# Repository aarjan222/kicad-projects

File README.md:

# kicad-projects
Please read text file of each sub files if seen, like driLL_siZE.txt file.

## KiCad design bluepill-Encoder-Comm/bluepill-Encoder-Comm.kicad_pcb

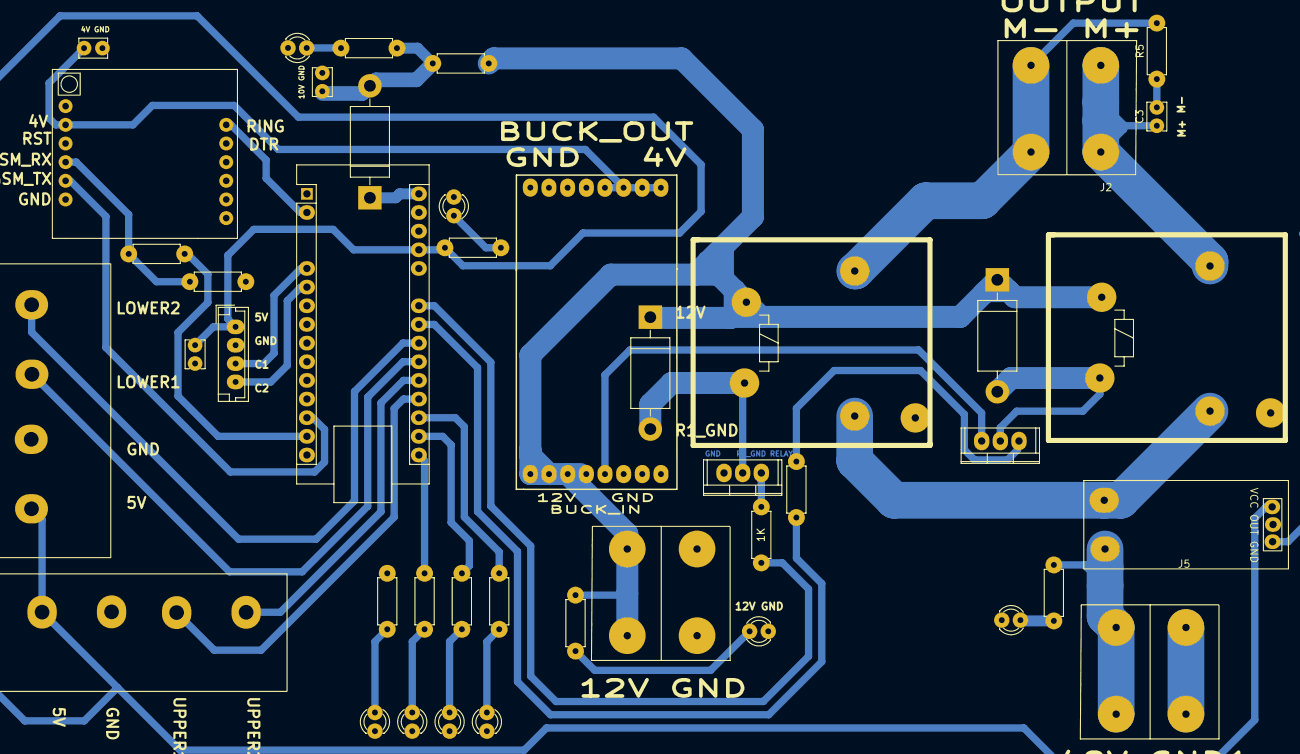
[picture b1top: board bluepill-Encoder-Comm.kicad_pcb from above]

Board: 2 copper layers, 43 parts (0 on the bottom side), 39 nets.

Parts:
1K: R; Resistor_small
A2: Arduino_Nano_v2.x; Arduino_Nano
C3, C4, C5, C6: C_Small; Capacitor_Disc_Small
D1, D2, D3: D_Small; Diode_Medium
D4, D5, D6, D7, D8, D9, D10, D11: LED; LED_D3.0mm
J2, J7, J11: Conn_01x02_Pin; Solar_Connector
J3, J4: Conn_01x04_Pin; Barrier_Terminal_Block
J5: Conn_02x03_Odd_Even; current sensor
J8: Conn_01x04; jst_4
Q1, Q2: TIP122; Voltage_Regulators
R1: 5; Resistor_small
R2, R3: 1K; Resistor_small
R4: 2K; Resistor_small
R5, R9, R10, R11, R12, R13: R_Small; Resistor_small
R6, R7, R8: 220; Resistor_small
Rly1, Rly2: 6V_Relay; Relay_HLS_MEDIUM
U1: SIM800L-CORE
U3: Buck; Buck_Regulator

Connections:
+4V: C5.1, U1.2 (VCC), U3.3 (OUT(+))
+5V: A2.27 (+5V), C6.1, J3.4, J4.4, J5.3, J8.1, R9.1
+10V: C4.1, D2.2 (A), R1.1, R8.1
+12V: D1.1 (K), D3.1 (K), J7.1, R1.2, R7.1, Rly1.2, Rly2.2, U3.1 (IN(+))
+48V: J5.1, J11.1, R6.1
/10V_regulated: A2.30 (VIN), D2.1 (K)
/+48V_I: J5.1, Rly1.1, Rly2.1
/C1: A2.5 (D2), J8.3
/C2: A2.6 (D3), J8.4
/GSM_RX: R2.1, R4.1, U1.4 (RXD)
/GSM_TX: A2.13 (D10), U1.5 (TXD)
/I1: A2.17 (3V3), R10.1
/I2: A2.18 (AREF), R11.1
/I3: A2.16 (D13), R12.1
/LOWER1: A2.21 (A2), J4.2
/LOWER2: A2.22 (A3), J4.1
/M+: C3.1, J2.1
/M-: J2.2, R5.2, Rly2.7
/R1_GND: D1.2 (A), Q1.2 (C), Rly1.6
/R2_GND: D3.2 (A), Q2.2 (C), Rly2.6
/RELAY1: A2.23 (A4), R3.1
/RELAY2: 1K.1, A2.24 (A5)
/RING: A2.2 (D0/RX), U1.12 (RING)
/UPPER1: A2.20 (A1), J3.1
/UPPER2: A2.19 (A0), J3.2
GND: A2.29 (GND), C4.2, C5.2, C6.2, D5.1 (K), D6.1 (K), D7.1 (K), D8.1 (K), D9.1 (K), D10.1 (K), D11.1 (K), J3.3, J4.3, J5.5, J7.2, J8.2, Q1.3 (E), Q2.3 (E), R4.2, U1.6 (GND), U3.2 (IN(-)), U3.4 (OUT(-))
GND1: D4.1 (K), J11.2, Rly1.14, Rly2.14
unnamed: A2.14 (D11), R2.2
unnamed: C3.2, R5.1
unnamed: D4.2 (A), R6.2
unnamed: D5.2 (A), R7.2
unnamed: D6.2 (A), R8.2
unnamed: D7.2 (A), R9.2
unnamed: D8.2 (A), R10.2
unnamed: D9.2 (A), R11.2
unnamed: D10.2 (A), R12.2
unnamed: D11.2 (A), R13.2
unnamed: Q1.1 (B), R3.2
unnamed: 1K.2, Q2.1 (B)

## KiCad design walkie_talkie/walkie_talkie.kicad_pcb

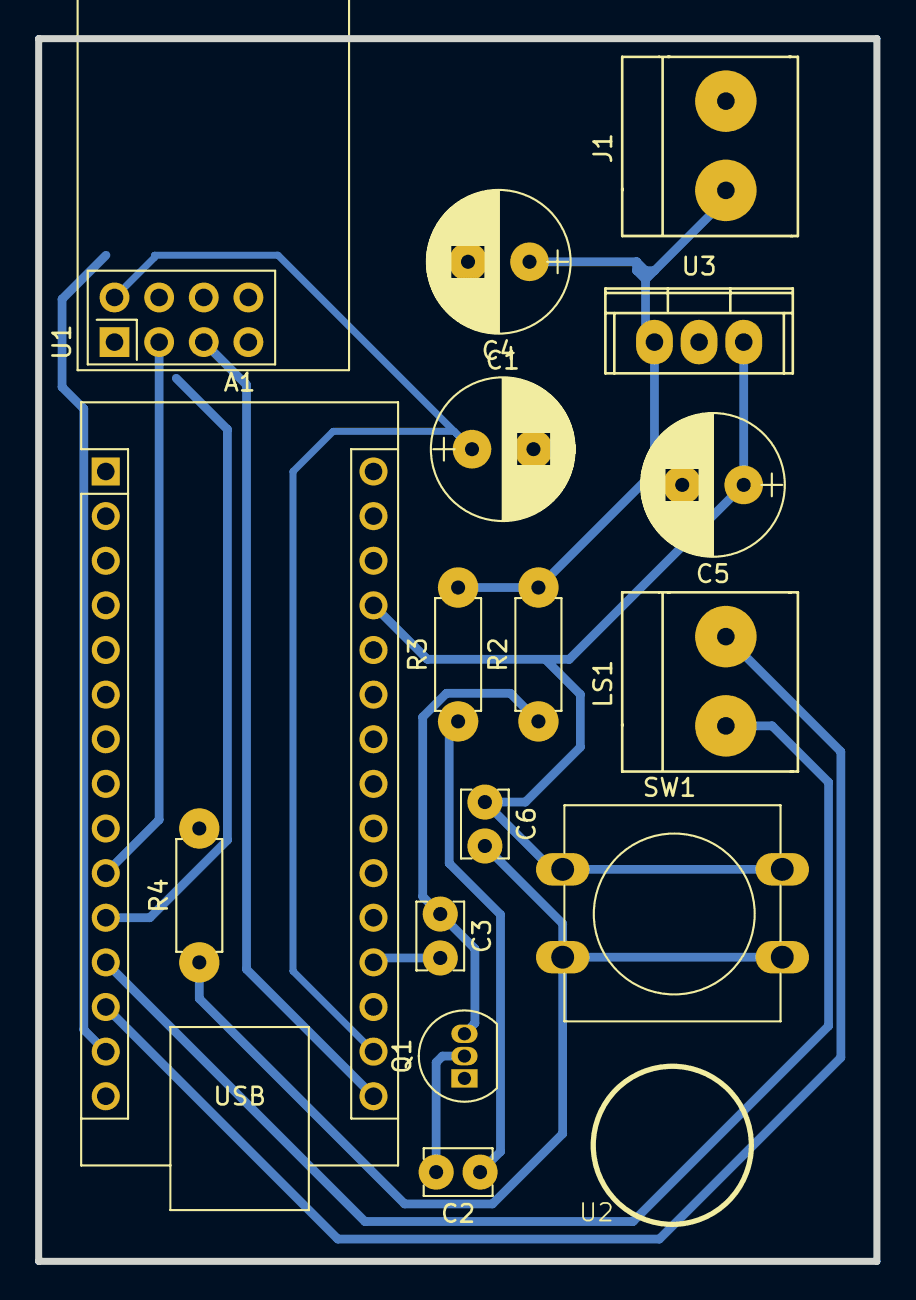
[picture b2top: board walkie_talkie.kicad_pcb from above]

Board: 2 copper layers, 47.7 x 69.6 mm, 17 parts (0 on the bottom side), 17 nets.

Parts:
A1: Arduino_Nano_Every; Arduino_Nano
C1, C4, C5: 100uF; Capacitor_100uF
C2, C3: 0.1u(104); Capacitor_Disc_Small
C6: 100nF; Capacitor_Disc_Small
J1: Conn_01x02; Connector_Bornier_2
LS1: Speaker; Connector_Bornier_2
Q1: 2N3904; TO-92_Inline
R2, R3, R4: 10K; Resistor_small
SW1: SW_Push_Dual; SW_PUSH-12mm
U1: NRF24L01_Breakout; nRF24L01_Breakout
U2: MicroPhone; mic
U3: L7805; Voltage_Regulators

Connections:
+3V3: A1.17 (3V3), C1.1, U1.2 (VCC)
+5V: A1.27 (+5V), C5.1, C6.1, SW1.1, U3.3 (OUT)
+9V: C4.1, J1.1, R2.2, R3.2, U3.1 (IN)
/A0: A1.19 (A0), C3.2
/CE: A1.10 (D7), U1.3 (CE)
/CSN: A1.11 (D8), U1.4 (~CSN)
/D3: A1.6 (D3), C6.2, R4.1, SW1.2
/IRQ: A1.5 (D2), U1.8 (IRQ)
/MISO: A1.15 (MISO), U1.7 (MISO)
/MOSI: A1.14 (MOSI), U1.6 (MOSI)
/SCK: A1.16 (SCK), U1.5 (SCK)
GND: A1.4 (GND), A1.29 (GND), C1.2, C4.2, C5.2, J1.2, Q1.1 (E), R4.2, U1.1 (GND), U3.2 (GND)
unnamed: A1.12 (D9), LS1.1
unnamed: A1.13 (D10), LS1.2
unnamed: C2.2, Q1.2 (B)
unnamed: C3.1, Q1.3 (C), R2.1
unnamed: C2.1, R3.1

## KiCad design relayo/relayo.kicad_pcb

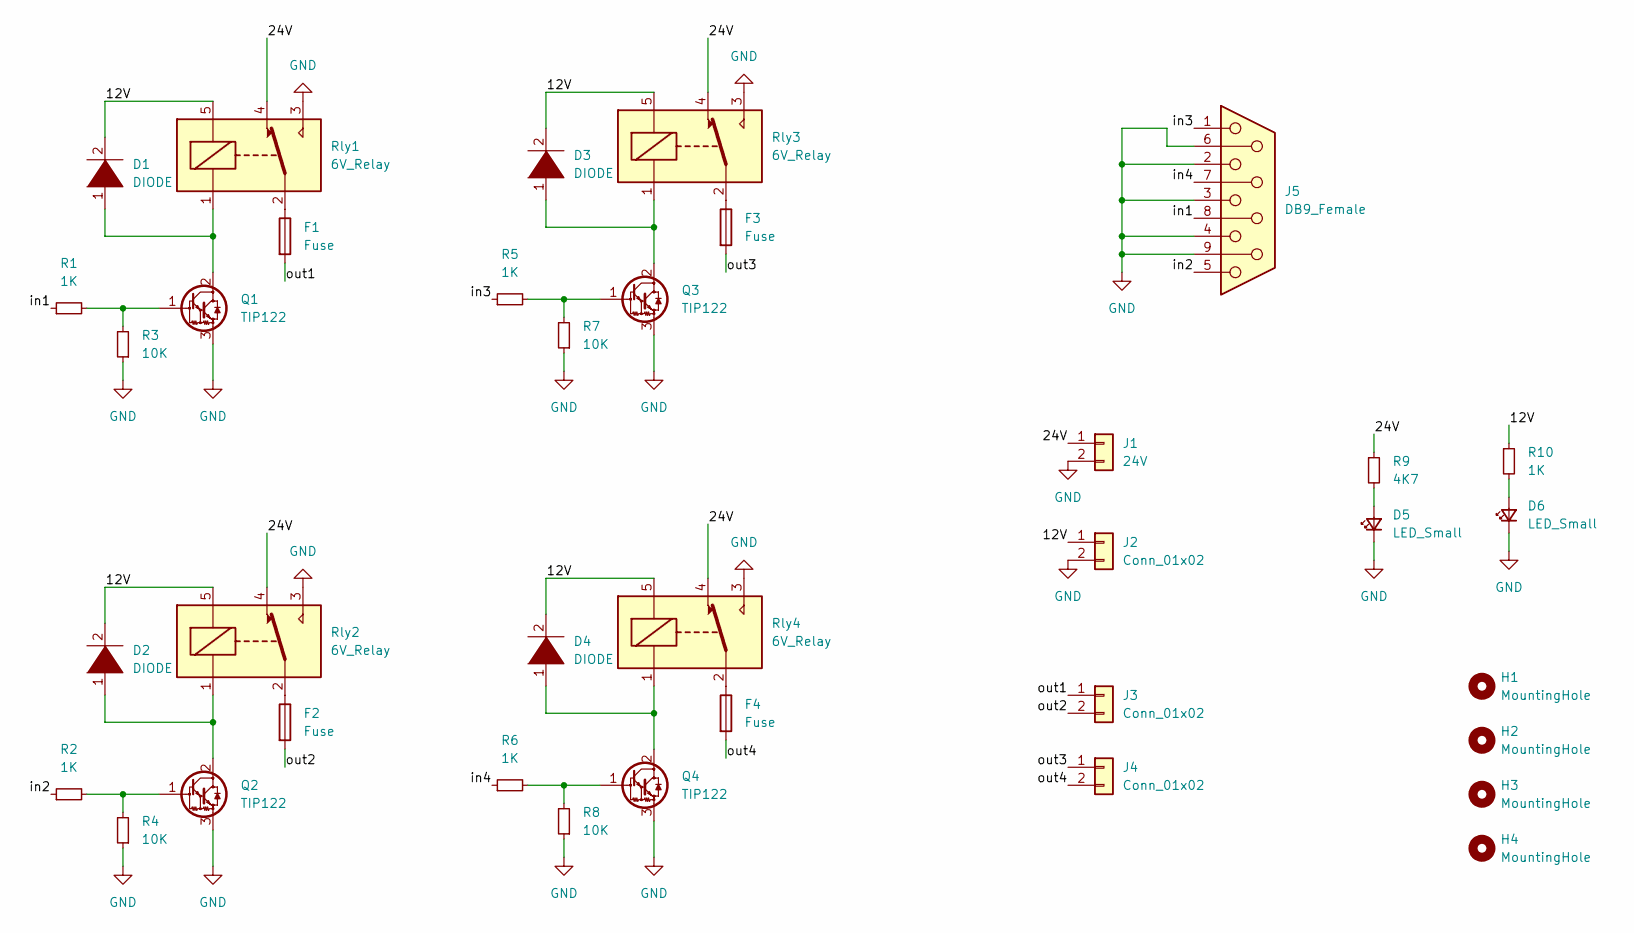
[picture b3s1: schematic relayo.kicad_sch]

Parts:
D1, D2, D3, D4: DIODE; Diode_Medium
D5, D6: LED_Small; LED_D3.0mm
F1, F2, F3, F4: Fuse; Fuse_Holder
H1, H2, H3, H4: MountingHole; MountingHole_4mm
J1: 24V; Solar_Connector
J2, J3, J4: Conn_01x02; Solar_Connector
J5: DB9_Female; Connector_DB_9
Q1, Q2, Q3, Q4: TIP122; TO-220-3_Vertical
R1, R2, R5, R6, R10: 1K; Resistor_small
R3, R4, R7, R8: 10K; Resistor_small
R9: 4K7; Resistor_small
Rly1, Rly2, Rly3, Rly4: 6V_Relay; Relay_HLS_MEDIUM

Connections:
/12V: D1.2 (A), D2.2 (A), D3.2 (A), D4.2 (A), J2.1, R10.1, Rly1.5, Rly2.5, Rly3.5, Rly4.5
/24V: J1.1, R9.1, Rly1.4, Rly2.4, Rly3.4, Rly4.4
/in1: J5.8, R1.1
/in2: J5.5, R2.1
/in3: J5.1, R5.1
/in4: J5.7, R6.1
/out1: F1.2, J3.1
/out2: F2.2, J3.2
/out3: F3.2, J4.1
/out4: F4.2, J4.2
GND: D5.1 (K), D6.1 (K), J1.2, J2.2, J5.2, J5.3, J5.4, J5.6, J5.9, Q1.3 (E), Q2.3 (E), Q3.3 (E), Q4.3 (E), R3.1, R4.1, R7.1, R8.1, Rly1.3, Rly2.3, Rly3.3, Rly4.3
unnamed: D1.1 (K), Q1.2 (C), Rly1.1
unnamed: D2.1 (K), Q2.2 (C), Rly2.1
unnamed: D3.1 (K), Q3.2 (C), Rly3.1
unnamed: D4.1 (K), Q4.2 (C), Rly4.1
unnamed: D5.2 (A), R9.2
unnamed: D6.2 (A), R10.2
unnamed: F1.1, Rly1.2
unnamed: F2.1, Rly2.2
unnamed: F3.1, Rly3.2
unnamed: F4.1, Rly4.2
unnamed: Q1.1 (B), R1.2, R3.2
unnamed: Q2.1 (B), R2.2, R4.2
unnamed: Q3.1 (B), R5.2, R7.2
unnamed: Q4.1 (B), R6.2, R8.2

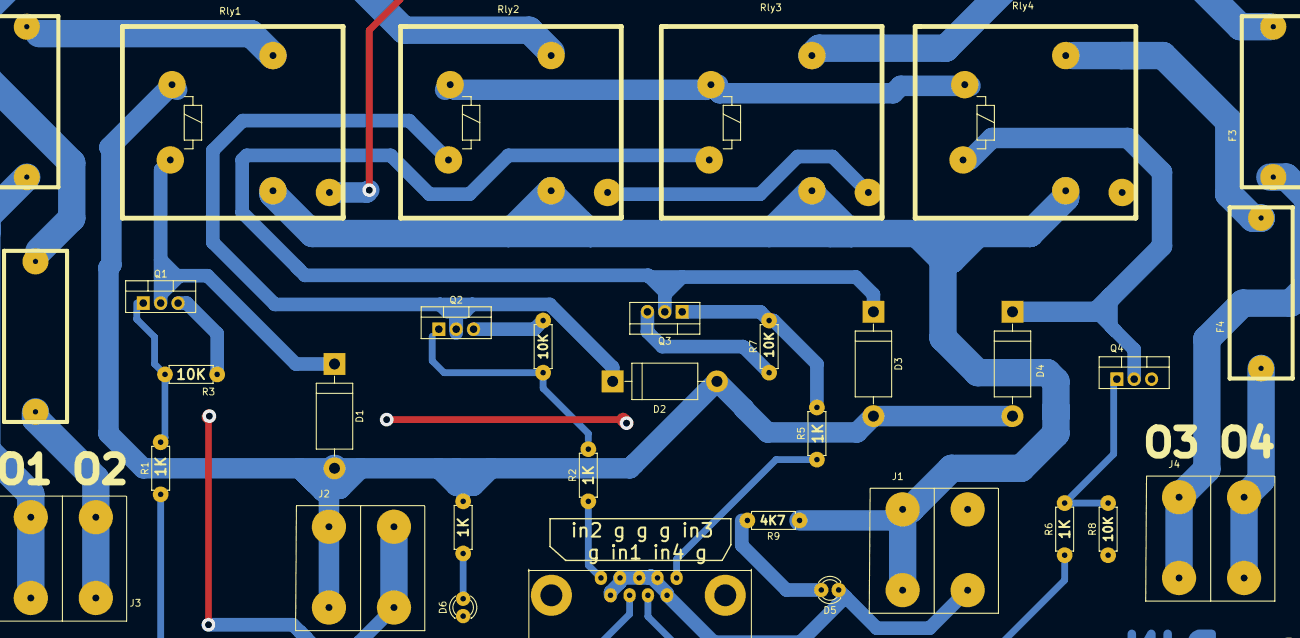
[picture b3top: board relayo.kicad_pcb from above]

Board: 2 copper layers, 37 parts (0 on the bottom side), 25 nets.

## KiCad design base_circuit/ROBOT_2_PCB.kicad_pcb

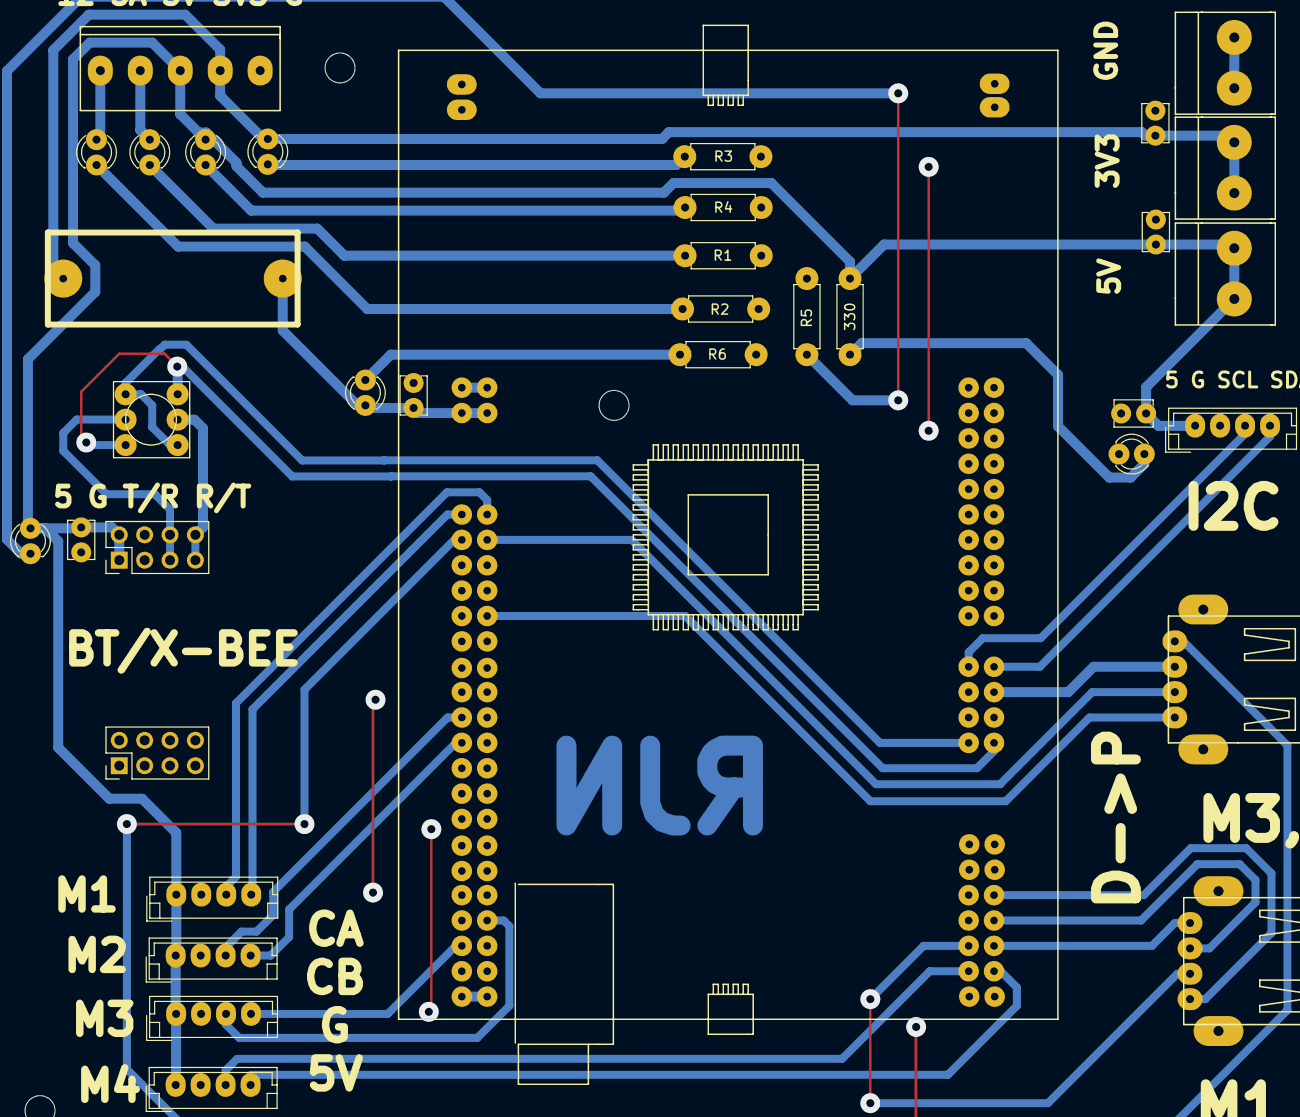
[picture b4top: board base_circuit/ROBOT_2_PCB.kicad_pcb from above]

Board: 2 copper layers, 43 parts (0 on the bottom side), 33 nets.

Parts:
C1, C2, C3: 104nF; Capacitor_Disc_Small
C4, C5: C_Small; Capacitor_Disc_Small
D1, D3, D4, D5, D6, D7: LED_Small; LED_D3.0mm
D2: LED; LED_D3.0mm
F1: Fuse_Small; Fuse_Holder
H1, H2, H3, H4, H5, H6, H7, H8: MountingHole; MountingHole_3mm
IMU1: Conn_01x04; jst_4
J1: Conn_01x04; PinHeader_2x04_P2.54mm_Vertical
J2, J6, J7: Conn_01x02_Male; Connector_Bornier_2
J3: Conn_01x01_Female; PinHeader_2x04_P2.54mm_Vertical
J4: M1,2; Connector_USB
J5: M3,4; Connector_USB
M1, M2, M3, M4: Conn_01x04_Female; jst_4
MPU1: 330; Resistor_small
POW_SPLY1: Conn_01x05; new_5_jst_bournier
R1, R2, R3, R4, R5, R6: R_Small; Resistor_small
S1: STM32F407_Discovery
SW2: SW_SPDT; DIP_Switch

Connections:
3V3: C5.1, D5.2 (A), F1.1, J6.1, J6.2, POW_SPLY1.4
5A: D3.2 (A), POW_SPLY1.2
5V: C2.1, C3.1, C4.1, D6.2 (A), D7.2 (A), IMU1.1, J1.1, J2.1, J2.2, M1.1, M2.1, M3.1, M4.1, MPU1.1, POW_SPLY1.3
12V: D4.2 (A), POW_SPLY1.1
GND: C1.2, C2.2, C3.2, C4.2, C5.2, D2.1 (K), IMU1.2, J1.3, J7.1, J7.2, M1.2, M2.2, M3.2, M4.2, POW_SPLY1.5, R1.2, R2.2, R3.2, R4.2, R5.1, R6.2, S1.1 (GND), S1.2 (GND), S1.23 (GND), S1.49 (GND), S1.50 (GND), S1.51 (GND), S1.52 (GND), S1.99 (GND), S1.100 (GND)
M1D: J4.1, S1.92 (PA13)
M2D: J4.3, S1.94 (PA9)
M3D: J5.1, S1.20 (PC4)
M4D: J5.3, S1.76 (PB5)
Motor_1_Enc_1: M1.3, S1.12 (PA0)
Motor_1_Enc_2: M1.4, S1.11 (PA1)
Motor_1_Pwm: J4.2, S1.95 (PC8)
Motor_2_Enc_1: M2.3, S1.27 (PE9)
Motor_2_Enc_2: M2.4, S1.29 (PE11)
Motor_2_Pwm: J4.4, S1.96 (PC9)
Motor_3_Enc_1: M3.3, S1.44 (PD12)
Motor_3_Enc_2: M3.4, S1.45 (PD13)
Motor_3_Pwm: J5.2, S1.14 (PA2)
Motor_4_Enc_1: M4.3, S1.97 (PC6)
Motor_4_Enc_2: M4.4, S1.98 (PC7)
Motor_4_Pwm: J5.4, S1.13 (PA3)
unnamed: D1.1 (K), R6.1
unnamed: D2.2 (A), MPU1.2
unnamed: D3.1 (K), R1.1
unnamed: D4.1 (K), R2.1
unnamed: D5.1 (K), R3.1
unnamed: D6.1 (K), R4.1
unnamed: D7.1 (K), R5.2
unnamed: J1.5, SW2.1 (A)
RX: S1.80 (PD6), SW2.2 (B)
SCL: IMU1.3, S1.73 (PB6)
SDA: IMU1.4, S1.74 (PB7)
VDD: C1.1, D1.2 (A), F1.2, S1.3 (VDD), S1.4 (VDD)

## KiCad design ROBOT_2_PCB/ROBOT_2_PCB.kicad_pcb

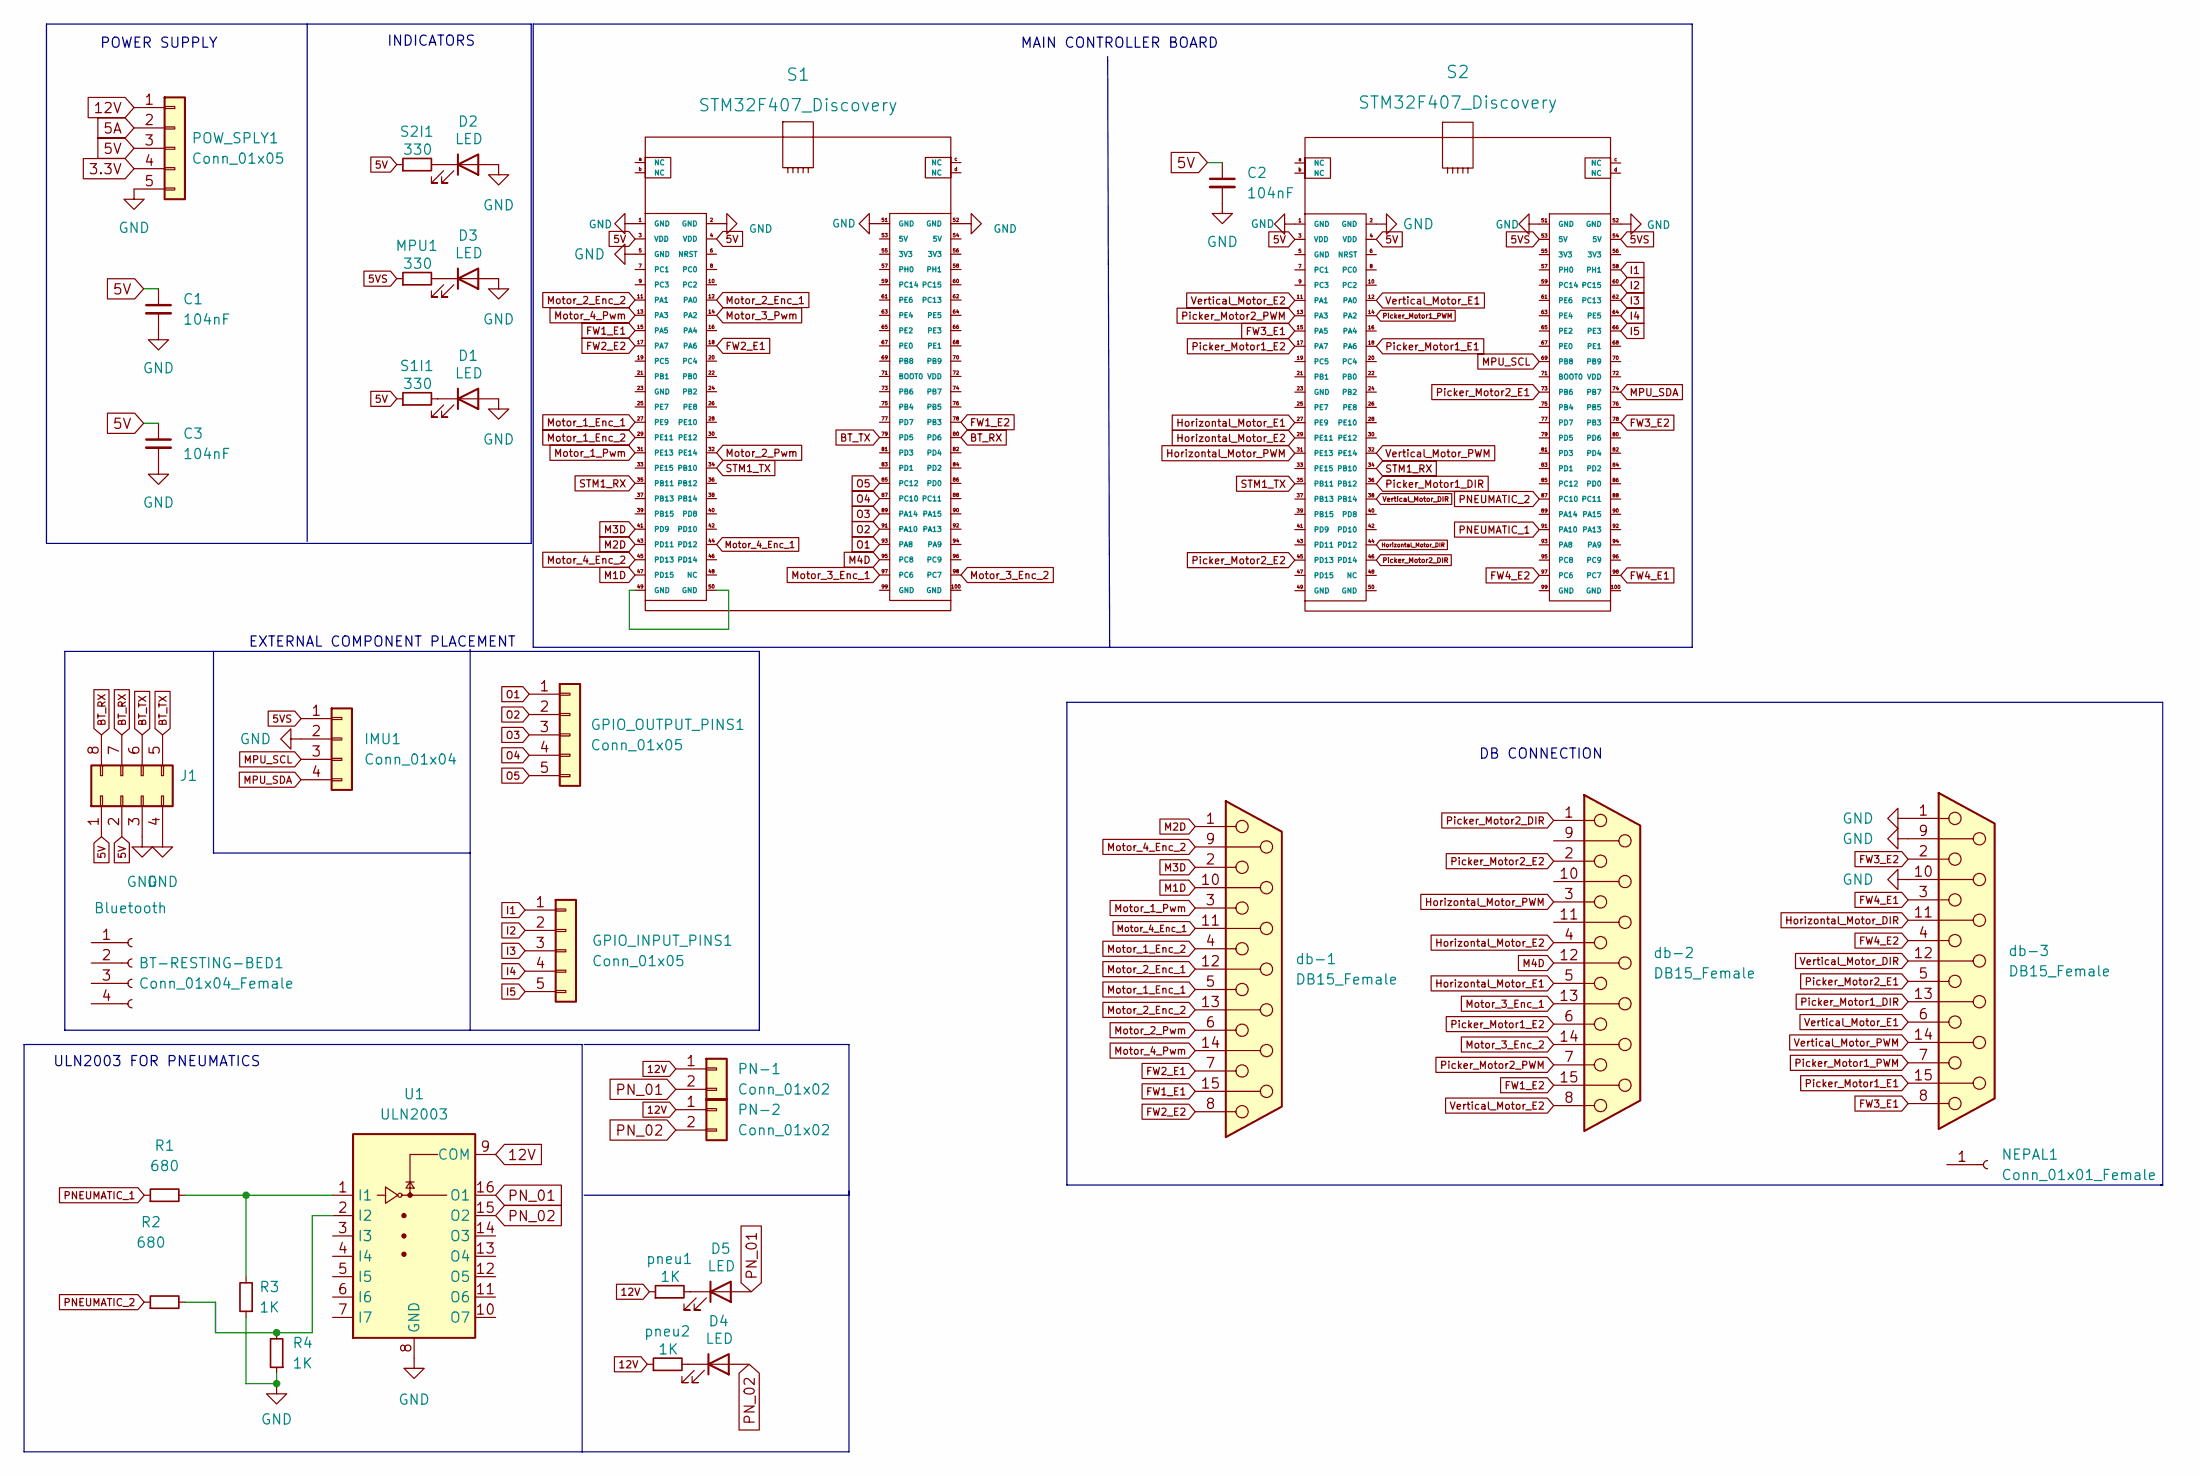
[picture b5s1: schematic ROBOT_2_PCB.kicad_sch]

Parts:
BT-RESTING-BED1: Conn_01x04_Female; PinHeader_2x04_P2.54mm_Vertical
C1, C2, C3: 104nF; Capacitor_Disc_Small
D1, D2, D3, D4, D5: LED; LED_D3.0mm
GPIO_INPUT_PINS1: Conn_01x05; new_5_jst_bournier
GPIO_OUTPUT_PINS1: Conn_01x05; new_5_jst_bournier
IMU1: Conn_01x04; jst_4
J1: Bluetooth; PinHeader_2x04_P2.54mm_Vertical
MPU1: 330; Resistor_small
NEPAL1: Conn_01x01_Female; nepalLogo
PN-1, PN-2: Conn_01x02; Connector_Bornier_2
POW_SPLY1: Conn_01x05; new_5_jst_bournier
R1, R2: 680; Resistor_small
R3, R4: 1K; Resistor_small
S1, S2: STM32F407_Discovery
S1I1, S2I1: 330; Resistor_small
U1: ULN2003; DIP-16_W7.62mm_Socket
db-1, db-2, db-3: DB15_Female; Connector_DB15
pneu1, pneu2: 1K; Resistor_small

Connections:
5V: C1.1, C2.1, C3.1, J1.1, J1.2, POW_SPLY1.3, S1.3 (VDD), S1.4 (VDD), S1I1.1, S2.3 (VDD), S2.4 (VDD), S2I1.1; also elsewhere on the board
5VS: IMU1.1, MPU1.1, S2.53 (5V), S2.54 (5V)
12V: PN-1.1, PN-2.1, POW_SPLY1.1, U1.9 (COM), pneu1.1, pneu2.1; also elsewhere on the board
BT_RX: J1.7, J1.8, S1.80 (PD6)
BT_TX: J1.5, J1.6, S1.79 (PD5)
FW1_E1: S1.15 (PA5), db-1.15
FW1_E2: S1.78 (PB3), db-2.15
FW2_E1: S1.18 (PA6), db-1.7
FW2_E2: S1.17 (PA7), db-1.8
FW3_E1: S2.15 (PA5), db-3.8
FW3_E2: S2.78 (PB3), db-3.2
FW4_E1: S2.98 (PC7), db-3.3
FW4_E2: S2.97 (PC6), db-3.4
GND: C1.2, C2.2, C3.2, D1.2 (A), D2.2 (A), D3.2 (A), IMU1.2, J1.3, J1.4, POW_SPLY1.5, R3.1, R4.1, S1.1 (GND), S1.2 (GND), S1.5 (GND), S1.51 (GND), S1.52 (GND), S2.1 (GND), S2.2 (GND), S2.51 (GND), S2.52 (GND), U1.8 (GND), db-3.1, db-3.9, db-3.10; also elsewhere on the board
Horizontal_Motor_DIR: S2.44 (PD12), db-3.11 (P111)
Horizontal_Motor_E1: S2.27 (PE9), db-2.5
Horizontal_Motor_E2: S2.29 (PE11), db-2.4
Horizontal_Motor_PWM: S2.31 (PE13), db-2.3
I1: GPIO_INPUT_PINS1.1, S2.58 (PH1)
I2: GPIO_INPUT_PINS1.2, S2.60 (PC15)
I3: GPIO_INPUT_PINS1.3, S2.62 (PC13)
I4: GPIO_INPUT_PINS1.4, S2.64 (PE5)
I5: GPIO_INPUT_PINS1.5, S2.66 (PE3)
M1D: S1.47 (PD15), db-1.10
M2D: S1.43 (PD11), db-1.1
M3D: S1.41 (PD9), db-1.2
M4D: S1.95 (PC8), db-2.12
MPU_SCL: IMU1.3, S2.69 (PB8)
MPU_SDA: IMU1.4, S2.74 (PB7)
Motor_1_Enc_1: S1.27 (PE9), db-1.5
Motor_1_Enc_2: S1.29 (PE11), db-1.4
Motor_1_Pwm: S1.31 (PE13), db-1.3
Motor_2_Enc_1: S1.12 (PA0), db-1.12
Motor_2_Enc_2: S1.11 (PA1), db-1.13
Motor_2_Pwm: S1.32 (PE14), db-1.6
Motor_3_Enc_1: S1.97 (PC6), db-2.13
Motor_3_Enc_2: S1.98 (PC7), db-2.14
Motor_3_Pwm: S1.14 (PA2)
Motor_4_Enc_1: S1.44 (PD12), db-1.11 (P111)
Motor_4_Enc_2: S1.45 (PD13), db-1.9
Motor_4_Pwm: S1.13 (PA3), db-1.14
unnamed: D1.1 (K), S1I1.2
unnamed: D2.1 (K), S2I1.2
unnamed: D3.1 (K), MPU1.2
unnamed: D4.1 (K), pneu2.2
unnamed: D5.1 (K), pneu1.2
unnamed: R1.2, R3.2, U1.1 (I1)
unnamed: R2.2, R4.2, U1.2 (I2)
unnamed: S1.49 (GND), S1.50 (GND)
O1: GPIO_OUTPUT_PINS1.1, S1.93 (PA8)
O2: GPIO_OUTPUT_PINS1.2, S1.91 (PA10)
O3: GPIO_OUTPUT_PINS1.3, S1.89 (PA14)
O4: GPIO_OUTPUT_PINS1.4, S1.87 (PC10)
O5: GPIO_OUTPUT_PINS1.5, S1.85 (PC12)
PNEUMATIC_1: R1.1, S2.89 (PA14), S2.91 (PA10)
PNEUMATIC_2: R2.1, S2.87 (PC10)
PN_01: D5.2 (A), PN-1.2, U1.16 (O1)
PN_02: D4.2 (A), PN-2.2, U1.15 (O2)
Picker_Motor1_DIR: S2.36 (PB12), db-3.13
Picker_Motor1_E1: S2.18 (PA6), db-3.15
Picker_Motor1_E2: S2.17 (PA7), db-2.6
Picker_Motor1_PWM: S2.14 (PA2), db-3.7
Picker_Motor2_DIR: S2.46 (PD14), db-2.1
Picker_Motor2_E1: S2.73 (PB6), db-3.5
Picker_Motor2_E2: S2.45 (PD13), db-2.2
Picker_Motor2_PWM: S2.13 (PA3), db-2.7
STM1_RX: S1.35 (PB11), S2.34 (PB10)
STM1_TX: S1.34 (PB10), S2.35 (PB11)
Vertical_Motor_DIR: S2.38 (PB14), db-3.12
Vertical_Motor_E1: S2.12 (PA0), db-3.6
Vertical_Motor_E2: S2.11 (PA1), db-2.8
Vertical_Motor_PWM: S2.32 (PE14), db-3.14

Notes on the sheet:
MAIN CONTROLLER BOARD
EXTERNAL COMPONENT PLACEMENT
INDICATORS
ULN2003 FOR PNEUMATICS
POWER SUPPLY
DB CONNECTION

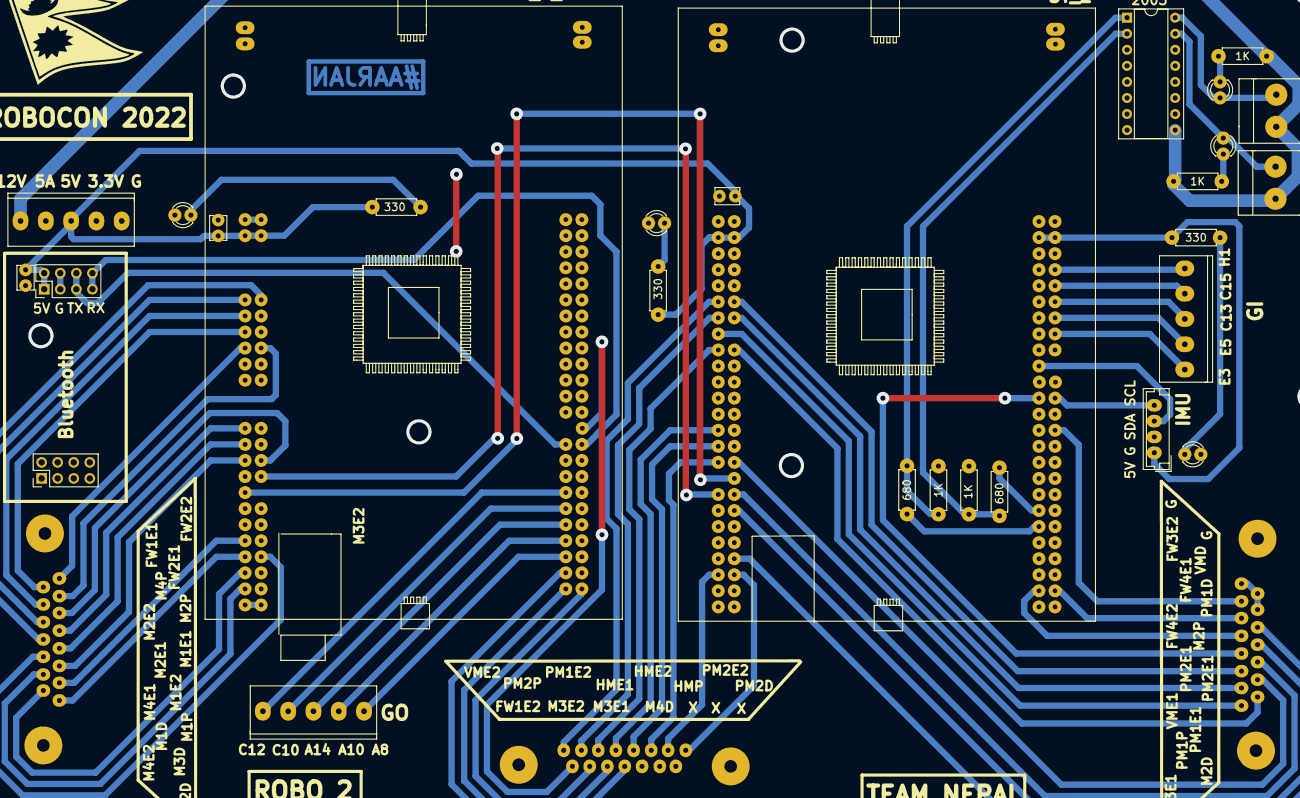
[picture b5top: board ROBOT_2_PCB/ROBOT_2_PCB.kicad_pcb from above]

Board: 2 copper layers, 32 parts (0 on the bottom side), 71 nets.

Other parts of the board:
POWER_SUPPLY1: Conn_01x05; new_5_jst_bournier

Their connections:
5V: POWER_SUPPLY1.3; also elsewhere on the board
12V: POWER_SUPPLY1.1; also elsewhere on the board
GND: POWER_SUPPLY1.5; also elsewhere on the board

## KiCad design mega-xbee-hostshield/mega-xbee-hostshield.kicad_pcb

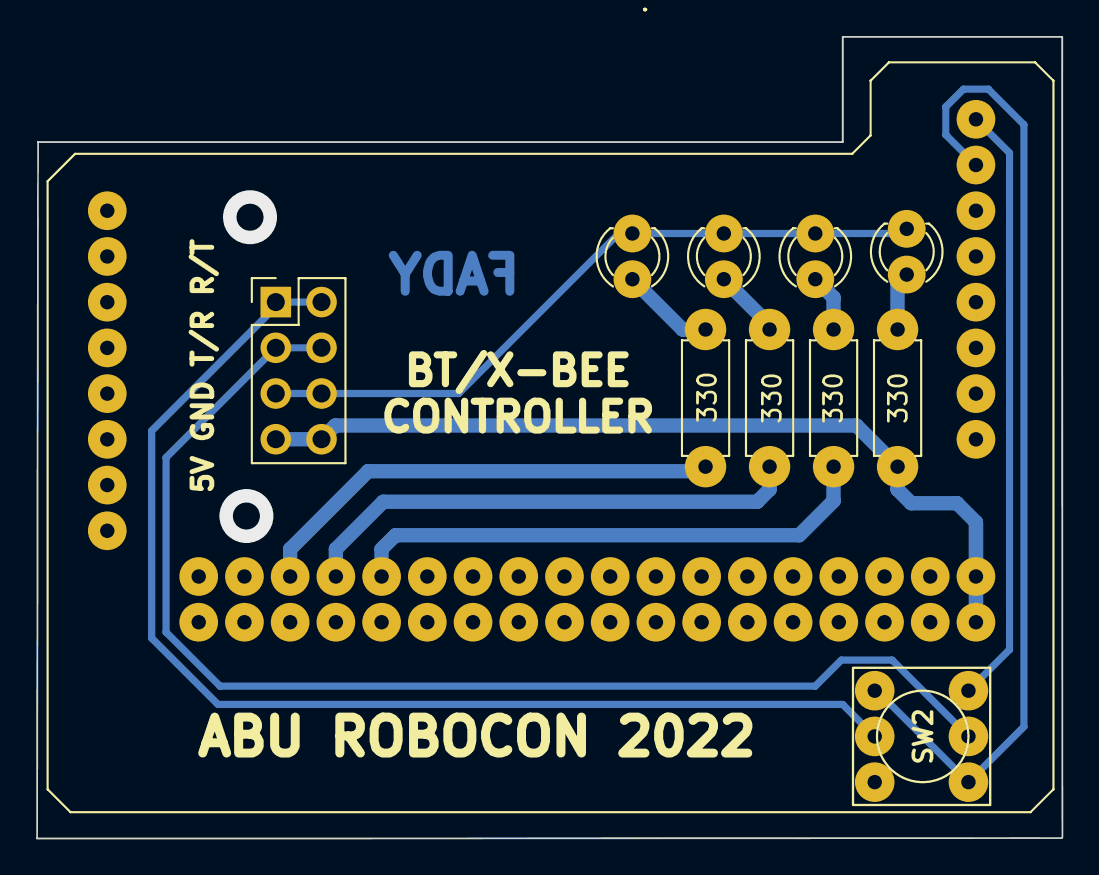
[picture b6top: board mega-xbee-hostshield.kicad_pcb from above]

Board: 2 copper layers, 57.0 x 44.5 mm, 11 parts (0 on the bottom side), 13 nets.

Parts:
D1: L1; LED_D3.0mm
D2: L2; LED_D3.0mm
D3, D4: L3; LED_D3.0mm
J1: Conn_02x04_Odd_Even; PinHeader_2x04_P2.54mm_Vertical
R1, R2, R3, R4: 330; Resistor_small
SW2: SW_SPDT; DIP_Switch
U1: Arduino_Mega2560_Shield

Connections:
5V: J1.7, J1.8, R4.1
GND: D1.1 (K), D2.1 (K), D3.1 (K), D4.1 (K), J1.5
LED1: R1.1, U1.50 (B3(MISO))
LED2: R2.1, U1.48 (L1(ICP5))
LED3: R3.1, U1.46 (L3(OC5A))
unnamed: D1.2 (A), R1.2
unnamed: D2.2 (A), R2.2
unnamed: D3.2 (A), R3.2
unnamed: D4.2 (A), R4.2
unnamed: J1.1, J1.2, SW2.5
unnamed: J1.3, J1.4, SW2.1 (A)
RX: SW2.2 (B), U1.14 (J1(TX3))
TX: SW2.3 (C), U1.15 (J0(RX3))

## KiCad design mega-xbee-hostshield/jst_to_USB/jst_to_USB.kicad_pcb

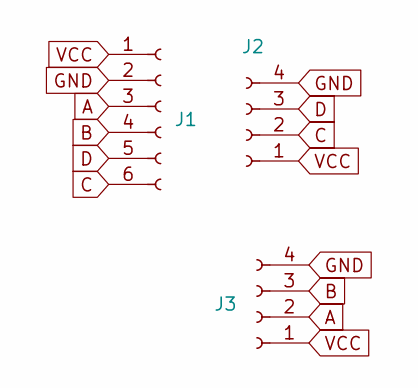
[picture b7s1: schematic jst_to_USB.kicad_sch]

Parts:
J1: Conn_01x06_Female; JST_EH_B6B-EH-A_1x06_P2.50mm_Vertical
J2, J3: Conn_01x04_Female; Connector_USB

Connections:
A: J1.3, J3.2
B: J1.4, J3.3
C: J1.6, J2.2
D: J1.5, J2.3
GND: J1.2, J2.4, J3.4
VCC: J1.1, J2.1, J3.1

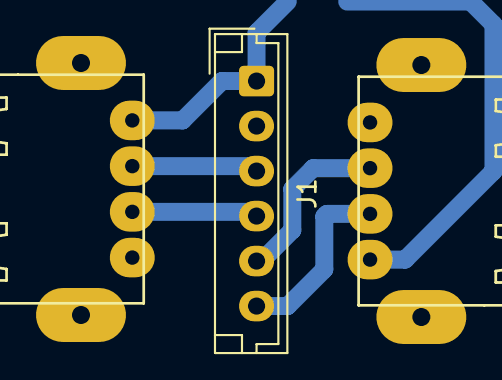
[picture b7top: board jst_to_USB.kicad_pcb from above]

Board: 2 copper layers, 3 parts (0 on the bottom side), 6 nets.

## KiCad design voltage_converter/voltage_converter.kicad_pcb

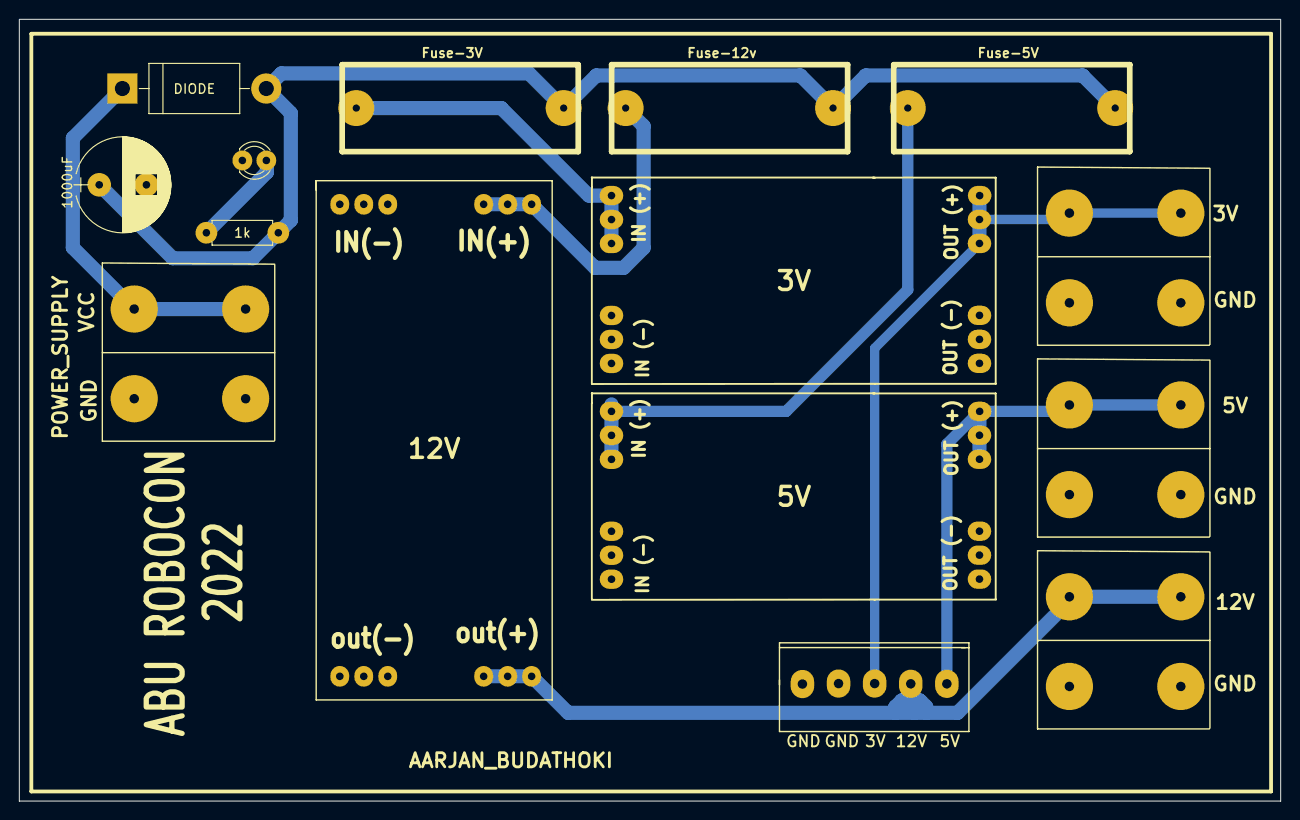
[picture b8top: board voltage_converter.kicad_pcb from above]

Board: 2 copper layers, 133.6 x 82.8 mm, 15 parts (0 on the bottom side), 10 nets.

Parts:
C1: 1000uF; Capacitor_1000uF
D1: DIODE; Diode_Medium
D2: LED; LED_D3.0mm
F1: Fuse-3V; Fuse_Holder
F2: Fuse-12v; Fuse_Holder
F3: Fuse-5V; Fuse_Holder
J1, J2, J3, J4: Conn_01x02_Female; Solar_Connector
J5: Conn_01x05_Male; JST_5_BIG
R1: 1k; Resistor_small
U1: Buck-3V; Buck_Regulator
U2: Buck-12V; Buck_5A
U3: Buck-5V; Buck_Regulator

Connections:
/3V: J2.1, J5.3, U1.4 (OUT(-))
/5V: J4.1, J5.5, U3.4 (OUT(-))
/12V: J3.1, J5.4, U2.3 (OUT(+))
/A: C1.1, D1.2 (A), F1.1, F2.1, F3.1, R1.2
GND: C1.2, D2.1 (K), J1.2, J2.2, J3.2, J4.2, J5.1, J5.2, U1.2 (IN(-)), U1.3 (OUT(+)), U2.1 (IN(+)), U2.4 (OUT(-)), U3.2 (IN(-)), U3.3 (OUT(+))
unnamed: D2.2 (A), R1.1
unnamed: F1.2, U1.1 (IN(+))
unnamed: F2.2, U2.2 (IN(-))
unnamed: F3.2, U3.1 (IN(+))
VCC: D1.1 (K), J1.1

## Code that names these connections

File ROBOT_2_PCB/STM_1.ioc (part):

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Mcu.Name=STM32F407V(E-G)Tx
Mcu.Package=LQFP100
Mcu.UserName=STM32F407VGTx
PA0-WKUP.GPIOParameters=GPIO_Label
PA0-WKUP.GPIO_Label=M2_E1
PA0-WKUP.Signal=S_TIM5_CH1
PA1.GPIOParameters=GPIO_Label
PA1.GPIO_Label=M2_E2
PA1.Signal=S_TIM5_CH2
PA10.GPIOParameters=GPIO_Label
PA10.GPIO_Label=O2
PA10.Signal=GPIO_Output
PA14.GPIOParameters=GPIO_Label
PA14.GPIO_Label=O3
PA14.Signal=GPIO_Output
PA2.GPIOParameters=GPIO_Label
PA2.GPIO_Label=M3_P
PA2.Signal=S_TIM2_CH3
PA3.GPIOParameters=GPIO_Label
PA3.GPIO_Label=M4_P
PA3.Signal=S_TIM2_CH4
PA5.Signal=S_TIM2_CH1_ETR
PA6.GPIOParameters=GPIO_Label
PA6.GPIO_Label=FW1_E1
PA6.Signal=S_TIM3_CH1
PA7.GPIOParameters=GPIO_Label
PA7.GPIO_Label=FW2_E2
PA7.Signal=S_TIM3_CH2
PA8.GPIOParameters=GPIO_Label
PA8.GPIO_Label=O1
PA8.Signal=GPIO_Output
PB10.GPIOParameters=GPIO_Label
PB10.GPIO_Label=ST1_TX
PB10.Mode=Asynchronous
PB10.Signal=USART3_TX
PB11.GPIOParameters=GPIO_Label
PB11.GPIO_Label=ST1_RX
PB11.Mode=Asynchronous
PB11.Signal=USART3_RX
PB3.GPIOParameters=GPIO_Label
PB3.GPIO_Label=FW1_E2
PB3.Signal=S_TIM2_CH2
PB6.Mode=I2C
PB6.Signal=I2C1_SCL
PB7.Mode=I2C
PB7.Signal=I2C1_SDA
PC10.GPIOParameters=GPIO_Label
PC10.GPIO_Label=O4
PC10.Signal=GPIO_Output
PC12.GPIOParameters=GPIO_Label
PC12.GPIO_Label=O5
PC12.Signal=GPIO_Output
PC4.Signal=GPIO_Output
PC6.GPIOParameters=GPIO_Label
PC6.GPIO_Label=M3_E1
PC6.Signal=S_TIM8_CH1
PC7.GPIOParameters=GPIO_Label
PC7.GPIO_Label=M3_E2
PC7.Signal=S_TIM8_CH2
PC8.GPIOParameters=GPIO_Label
PC8.GPIO_Label=M4D
PC8.Signal=GPIO_Output
PD11.GPIOParameters=GPIO_Label
PD11.GPIO_Label=M2D
PD11.Signal=GPIO_Output
PD12.GPIOParameters=GPIO_Label
PD12.GPIO_Label=M4_E1
PD12.Signal=S_TIM4_CH1
PD13.GPIOParameters=GPIO_Label
PD13.GPIO_Label=M4_E2
PD13.Signal=S_TIM4_CH2
PD15.GPIOParameters=GPIO_Label
PD15.GPIO_Label=M1D
PD15.Signal=GPIO_Output
PD5.GPIOParameters=GPIO_Label
PD5.GPIO_Label=BT_TX
PD5.Mode=Asynchronous
PD5.Signal=USART2_TX
PD6.GPIOParameters=GPIO_Label
PD6.GPIO_Label=BT_RX
PD6.Mode=Asynchronous
PD6.Signal=USART2_RX
PD9.GPIOParameters=GPIO_Label
PD9.GPIO_Label=M3D
PD9.Signal=GPIO_Output
PE11.GPIOParameters=GPIO_Label
PE11.GPIO_Label=M1_E2
PE11.Signal=S_TIM1_CH2
PE13.GPIOParameters=GPIO_Label
PE13.GPIO_Label=M1_P
PE13.Signal=S_TIM1_CH3
PE14.GPIOParameters=GPIO_Label
PE14.GPIO_Label=M2_P
PE14.Signal=S_TIM1_CH4
PE9.GPIOParameters=GPIO_Label
PE9.GPIO_Label=M1_E1
PE9.Signal=S_TIM1_CH1
RCC.HSE_VALUE=8000000
RCC.SYSCLKFreq_VALUE=168000000
RCC.SYSCLKSource=RCC_SYSCLKSOURCE_PLLCLK
board=STM32F407G-DISC1
boardIOC=true

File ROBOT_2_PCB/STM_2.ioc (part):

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Mcu.Name=STM32F407V(E-G)Tx
Mcu.Package=LQFP100
Mcu.UserName=STM32F407VGTx
PA0-WKUP.GPIOParameters=GPIO_Label
PA0-WKUP.GPIO_Label=VME1
PA0-WKUP.Signal=S_TIM5_CH1
PA1.GPIOParameters=GPIO_Label
PA1.GPIO_Label=VME2
PA1.Signal=S_TIM5_CH2
PA13.Mode=Trace_Asynchronous_SW
PA13.Signal=SYS_JTMS-SWDIO
PA14.Mode=Trace_Asynchronous_SW
PA14.Signal=SYS_JTCK-SWCLK
PA2.GPIOParameters=GPIO_Label
PA2.GPIO_Label=PM1P
PA2.Signal=S_TIM2_CH3
PA3.GPIOParameters=GPIO_Label
PA3.GPIO_Label=PM2P
PA3.Signal=S_TIM2_CH4
PA6.GPIOParameters=GPIO_Label
PA6.GPIO_Label=PM1E1
PA6.Signal=S_TIM3_CH1
PA7.GPIOParameters=GPIO_Label
PA7.GPIO_Label=PM1E2
PA7.Signal=S_TIM3_CH2
PB10.GPIOParameters=GPIO_Label
PB10.GPIO_Label=STM2_TX
PB10.Mode=Asynchronous
PB10.Signal=USART3_TX
PB11.GPIOParameters=GPIO_Label
PB11.GPIO_Label=STM2_RX
PB11.Mode=Asynchronous
PB11.Signal=USART3_RX
PB12.GPIOParameters=GPIO_Label
PB12.GPIO_Label=Picker_Motor_1_DIR
PB12.Signal=GPIO_Output
PB14.GPIOParameters=GPIO_Label
PB14.GPIO_Label=Vertical_Motor_DIR
PB14.Signal=GPIO_Output
PB3.Mode=Trace_Asynchronous_SW
PB3.Signal=SYS_JTDO-SWO
PB6.GPIOParameters=GPIO_Label
PB6.GPIO_Label=PM2E1
PB6.Signal=S_TIM4_CH1
PB7.GPIOParameters=GPIO_Label
PB7.GPIO_Label=SDA
PB7.Mode=I2C
PB7.Signal=I2C1_SDA
PB8.GPIOParameters=GPIO_Label
PB8.GPIO_Label=SCL
PB8.Mode=I2C
PB8.Signal=I2C1_SCL
PC10.GPIOParameters=GPIO_Label
PC10.GPIO_Label=PNEUMATIC_2
PC10.Signal=GPIO_Output
PC13-ANTI_TAMP.GPIOParameters=GPIO_Label
PC13-ANTI_TAMP.GPIO_Label=I3
PC13-ANTI_TAMP.Signal=GPIO_Input
PC15-OSC32_OUT.GPIOParameters=GPIO_Label
PC15-OSC32_OUT.GPIO_Label=I2
PC15-OSC32_OUT.Signal=GPIO_Input
PC6.GPIOParameters=GPIO_Label
PC6.GPIO_Label=FW4_E1
PC6.Signal=S_TIM8_CH1
PC7.GPIOParameters=GPIO_Label
PC7.GPIO_Label=FW4_E2
PC7.Signal=S_TIM8_CH2
PD12.GPIOParameters=GPIO_Label
PD12.GPIO_Label=Horizontal_Motor_DIR
PD12.Signal=GPIO_Output
PD13.GPIOParameters=GPIO_Label
PD13.GPIO_Label=PM2E2
PD13.Signal=S_TIM4_CH2
PD14.GPIOParameters=GPIO_Label
PD14.GPIO_Label=Picker_Motor_2_DIR
PD14.Signal=GPIO_Output
PE11.GPIOParameters=GPIO_Label
PE11.GPIO_Label=HME2
PE11.Signal=S_TIM1_CH2
PE13.GPIOParameters=GPIO_Label
PE13.GPIO_Label=HMP
PE13.Signal=S_TIM1_CH3
PE14.GPIOParameters=GPIO_Label
PE14.GPIO_Label=VMP
PE14.Signal=S_TIM1_CH4
PE3.GPIOParameters=GPIO_Label
PE3.GPIO_Label=I5
PE3.Signal=GPIO_Input
PE5.GPIOParameters=GPIO_Label
PE5.GPIO_Label=I4
PE5.Signal=GPIO_Input
PE9.GPIOParameters=GPIO_Label
PE9.GPIO_Label=HME1
PE9.Signal=S_TIM1_CH1
PH1-OSC_OUT.GPIOParameters=GPIO_Label
PH1-OSC_OUT.GPIO_Label=I1
PH1-OSC_OUT.Signal=GPIO_Input
RCC.HSE_VALUE=8000000
RCC.SYSCLKFreq_VALUE=50000000
RCC.SYSCLKSource=RCC_SYSCLKSOURCE_PLLCLK
board=STM32F407G-DISC1
boardIOC=true

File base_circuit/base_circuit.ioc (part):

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Mcu.Name=STM32F407V(E-G)Tx
Mcu.Package=LQFP100
Mcu.UserName=STM32F407VGTx
PA0-WKUP.GPIOParameters=GPIO_Label
PA0-WKUP.GPIO_Label=M2_E1
PA0-WKUP.Signal=S_TIM2_CH1_ETR
PA1.GPIOParameters=GPIO_Label
PA1.GPIO_Label=M2_E2
PA1.Signal=S_TIM2_CH2
PA2.GPIOParameters=GPIO_Label
PA2.GPIO_Label=M3P
PA2.Signal=S_TIM5_CH3
PA3.GPIOParameters=GPIO_Label
PA3.GPIO_Label=M4P
PA3.Signal=S_TIM5_CH4
PA9.GPIOParameters=GPIO_Label
PA9.GPIO_Label=M1D
PA9.Signal=GPIO_Output
PB3.Signal=SYS_JTDO-SWO
PB5.GPIOParameters=GPIO_Label
PB5.GPIO_Label=M4D
PB5.Signal=GPIO_Output
PB6.Mode=I2C
PB6.Signal=I2C1_SCL
PB7.Mode=I2C
PB7.Signal=I2C1_SDA
PC4.GPIOParameters=GPIO_Label
PC4.GPIO_Label=M3D
PC4.Signal=GPIO_Output
PC6.GPIOParameters=GPIO_Label
PC6.GPIO_Label=M3_E1
PC6.Signal=S_TIM3_CH1
PC7.GPIOParameters=GPIO_Label
PC7.GPIO_Label=M3_E2
PC7.Signal=S_TIM3_CH2
PC8.GPIOParameters=GPIO_Label
PC8.GPIO_Label=M1P
PC8.Signal=S_TIM8_CH3
PC9.GPIOParameters=GPIO_Label
PC9.GPIO_Label=M2P
PC9.Signal=S_TIM8_CH4
PD12.GPIOParameters=GPIO_Label
PD12.GPIO_Label=M4_E1
PD12.Signal=S_TIM4_CH1
PD13.GPIOParameters=GPIO_Label
PD13.GPIO_Label=M4_E2
PD13.Signal=S_TIM4_CH2
PD5.GPIOParameters=GPIO_Label
PD5.GPIO_Label=BT_TX
PD5.Mode=Asynchronous
PD5.Signal=USART2_TX
PD6.GPIOParameters=GPIO_Label
PD6.GPIO_Label=BT_RX
PD6.Mode=Asynchronous
PD6.Signal=USART2_RX
PE11.GPIOParameters=GPIO_Label
PE11.GPIO_Label=M1_E2
PE11.Signal=S_TIM1_CH2
PE14.GPIOParameters=GPIO_Label
PE14.GPIO_Label=M2D
PE14.Signal=GPIO_Output
PE9.GPIOParameters=GPIO_Label
PE9.GPIO_Label=M1_E1
PE9.Signal=S_TIM1_CH1
RCC.HSE_VALUE=8000000
RCC.SYSCLKFreq_VALUE=168000000
RCC.SYSCLKSource=RCC_SYSCLKSOURCE_PLLCLK
board=STM32F407G-DISC1
boardIOC=true
